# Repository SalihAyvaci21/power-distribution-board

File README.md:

# power-distribution-board
This is a simple and efficient power distribution board originally designed for drones, later adapted for workshop use. It features LM7805 and LM2595 regulators and can be easily produced using basic acid etching techniques with commonly available components.

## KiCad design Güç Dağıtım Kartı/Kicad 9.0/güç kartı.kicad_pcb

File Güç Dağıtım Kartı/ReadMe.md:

# 🔋 Drone ve Atölye İçin Güç Dağıtım Kartı (PDB)

Bu proje, hem **drone sistemlerinin** güç ihtiyacını karşılamak hem de **elektronik atölyelerinde** kullanılmak üzere tasarlanmış, üretimi kolay ve kararlı bir Güç Dağıtım Kartıdır (Power Distribution Board).

Tasarım, farklı voltaj ve akım gereksinimi duyan modüller için (hem taşınabilir hem sabit uygulamalarda) güvenli ve esnek bir güç çözümü sunar. Özellikle asit baskı yöntemiyle ev ortamında hızlıca üretilebilecek şekilde optimize edilmiştir.

---

##  Proje Görselleri

Tasarımın çizim aşamasından üretim aşamasına kadar olan görselleri aşağıdadır:

|    **Devre Şeması (Schematic)**    |     **PCB Çizimi (Layout)**     |
| :--------------------------------: | :-----------------------------: |
|   |     |
| *LM7805 ve LM2595 Bağlantı Yapısı* | *Asit baskıya uygun yol çizimi* |

|         **3D Render Görüntüsü**         |     **Simülasyon (Simulation)**     |
| :-------------------------------------: | :---------------------------------: |
|               |  |
| *Bileşen yerleşimi ve soğutucu montajı* |          **Kart testleri *          |

---

## 🌟 Teknik Özellikler

u kart, geniş giriş voltajı aralığı ve çift çıkış kanalı (sabit + ayarlanabilir) ile çok yönlü bir kullanım sunar.

| Özellik | Değer / Açıklama |
| :--- | :--- |
| **Giriş Voltajı** | [cite_start]7V - 30V DC [cite: 10] |
| **Sabit Çıkış** | [cite_start]5V / 1.5A (LM7805 ile) [cite: 10, 11] |
| **Ayarlanabilir Çıkış** | [cite_start]1.2V - 25V / 2A (LM2595-ADJ ile) [cite: 10, 11] |
| **Koruma** | [cite_start]Ters kutup, Kısa devre, Aşırı yük koruması [cite: 10, 13] |
| **Üretim Yöntemi** | [cite_start]Asit kazıma (Toner transfer veya UV) [cite: 10, 14] |

---

## 🛠️ Devre Bileşenleri (BOM)

Proje, kolay bulunabilir temel elektronik bileşenler kullanılarak tasarlanmıştır :

* **Regülatörler:** LM7805 (Linear), LM2595-ADJ (Switching)
* **Diyot:** 1N5822 Schottky Diyot
* **İndüktör:** 33µH
* **Kapasitörler:** 470µF ve 100nF
* **Kontrol:** Voltaj ayarı için Potansiyometre
* **Bağlantı:** Terminal Bloklar
* **Soğutma:** Alüminyum profil soğutucu

---

## 🧪 Performans ve Test Sonuçları

Kart üzerinde yapılan laboratuvar testleri ve termal analiz sonuçları şöyledir:

* **Yük Testi:** 28V giriş voltajı altında uzun süreli çalışma testi başarıyla tamamlanmıştır.
* **Termal Analiz:** 1A yük altında 1 saatlik çalışmada (soğutucu ile) maksimum **~55°C** sıcaklığa ulaşmıştır.
* **Ripple (Dalgalanma):** Osiloskop ölçümlerinde çıkış dalgalanması **< 50mV** olarak ölçülmüştür.

---

## 🚀 Uygulama Alanları

Bu kartı aşağıdaki projelerde güç kaynağı olarak kullanabilirsiniz:

1.  **Drone Sistemleri:** Uçuş kontrolcüleri ve çevre birimlerini beslemek için.
2.  **Atölye Güç Kaynağı:** Prototip devreler için ayarlanabilir DC kaynak.
3.  **Gömülü Sistemler:** Test kartları ve sensör beslemeleri.
4.  **Aydınlatma:** Mobil şarj üniteleri ve LED sürücü devreleri.

---

## 📂 Dosya Yapısı

* `/Schematic` - Devre şeması ve PDF çıktıları.
* `/PCB` - Asit baskı için hazır PCB çizimleri (Gerber/PDF).
* `/Image` - Proje görselleri ve test fotoğrafları.

---

## 👨‍💻 Geliştirici

**Salih Tekin Ayvacı** 
* 📍 İstanbul, Türkiye 

Projeyle ilgili soru ve önerileriniz için LinkedIn veya GitHub üzerinden iletişime geçebilirsiniz.

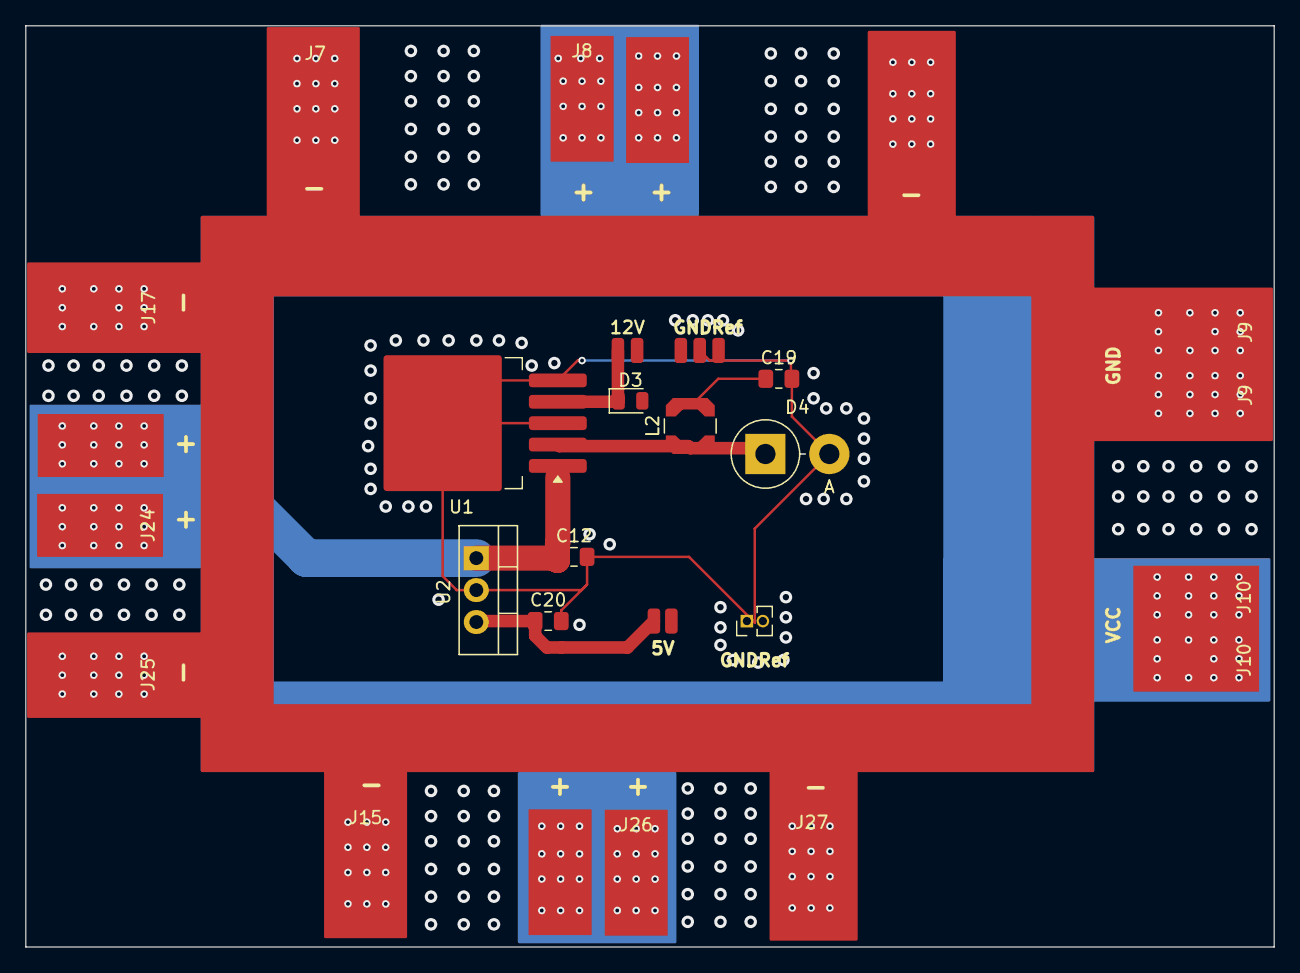
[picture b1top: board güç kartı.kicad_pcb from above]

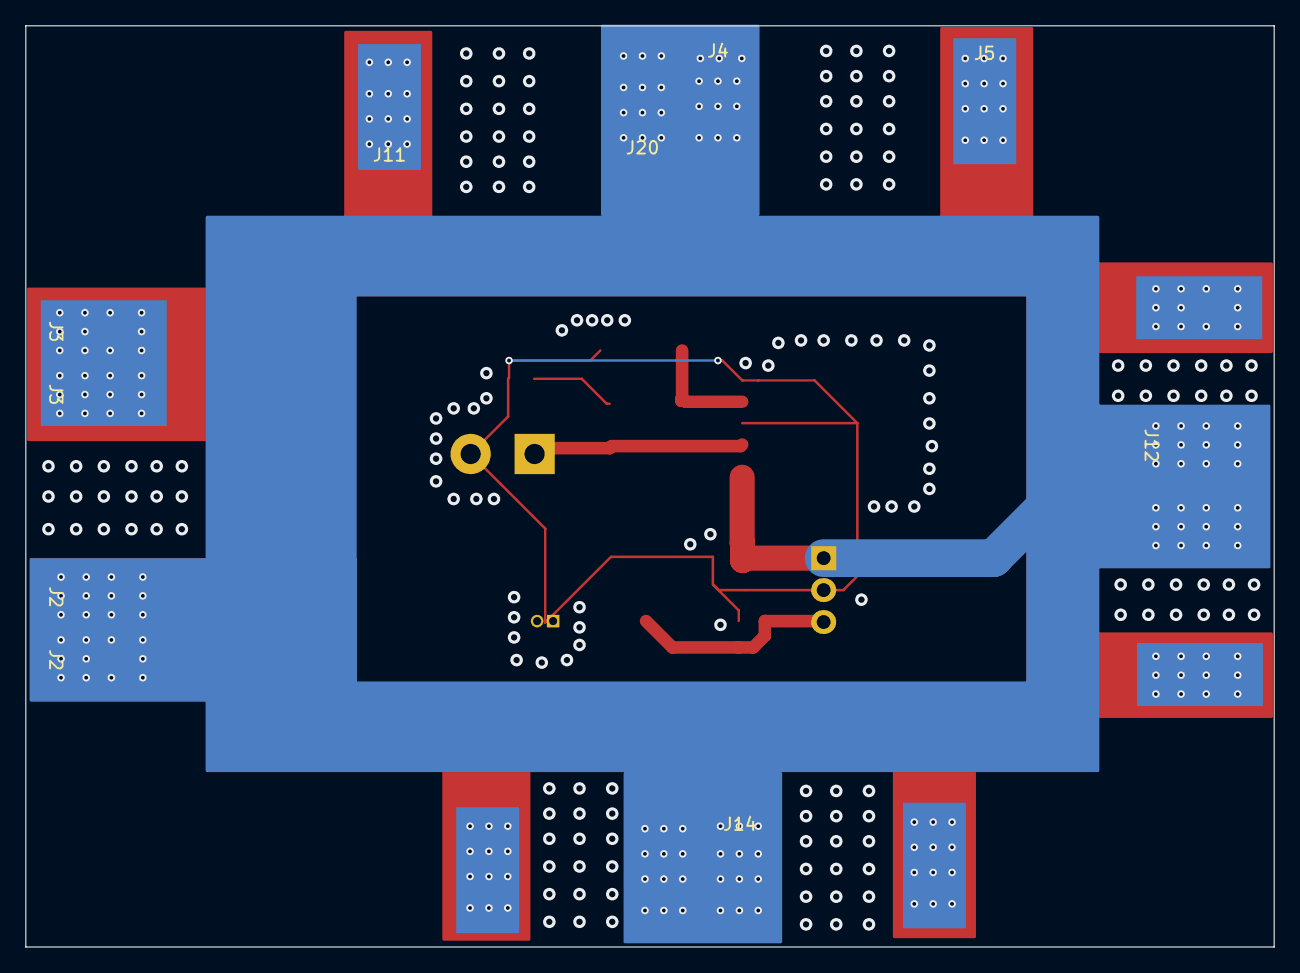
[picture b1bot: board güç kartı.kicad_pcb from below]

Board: 2 copper layers, 99.2 x 73.2 mm, 48 parts (16 on the bottom side), 7 nets.

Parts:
C12: 10uF; C_0805_2012Metric_Pad1.18x1.45mm_HandSolder
C19: 220uF; C_0805_2012Metric_Pad1.18x1.45mm_HandSolder
C20: 100uF; C_0805_2012Metric_Pad1.18x1.45mm_HandSolder
D3: D; D_0805_2012Metric
D4: 1N5822; D_DO-201AD_P5.08mm_Vertical_AnodeUp
J2, J2#2, J4, J12, J20: VCC; SolderWirePad_1x01_SMD_5x10mm
J3, J3#2, J5, J7, J9, J9#2, J11, J13, J15, J17, J19, J21, J23, J25, J27, J29: GND; SolderWirePad_1x01_SMD_5x10mm
J8, J10, J10#2, J14, J16, J18, J22, J24, J26, J28, J30: Conn_01x01_Socket; SolderWirePad_1x01_SMD_5x10mm
J34, J37, J38, J39, J40, J44, J45: Conn_01x01; SolderWirePad_1x01_SMD_1x2mm
J36: Conn_01x02; PinHeader_1x02_P1.27mm_Vertical
L2: 33uH; L_Coilcraft_LPS4018
U1: LM2596S-12; TO-263-5_TabPin3
U2: LM7805_TO220; TO-220-3_Vertical

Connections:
5V: C20.1, J34.1, J38.1, U2.3 (VO)
12V: D3.1 (K), J37.1, J44.1, U1.4 (FB)
GND: J3.1, J3#2.1, J5.1, J7.1, J9.1, J9#2.1, J11.1, J13.1, J15.1, J17.1, J19.1, J21.1, J23.1, J25.1, J27.1, J29.1
GNDREF: C12.2, C19.2, C20.2, D4.2 (A), J36.1, J36.2, J39.1, J40.1, J45.1, U1.3 (GND), U1.5 (~ON/OFF), U2.2 (GND)
unnamed: C19.1, D3.2 (A), L2.2
unnamed: D4.1 (K), L2.1, U1.2 (OUT)
VIN: C12.1, J2.1, J2#2.1, J4.1, J8.1, J10.1, J10#2.1, J12.1, J14.1, J16.1, J18.1, J20.1, J22.1, J24.1, J26.1, J28.1, J30.1, U1.1 (VIN), U2.1 (VI)
